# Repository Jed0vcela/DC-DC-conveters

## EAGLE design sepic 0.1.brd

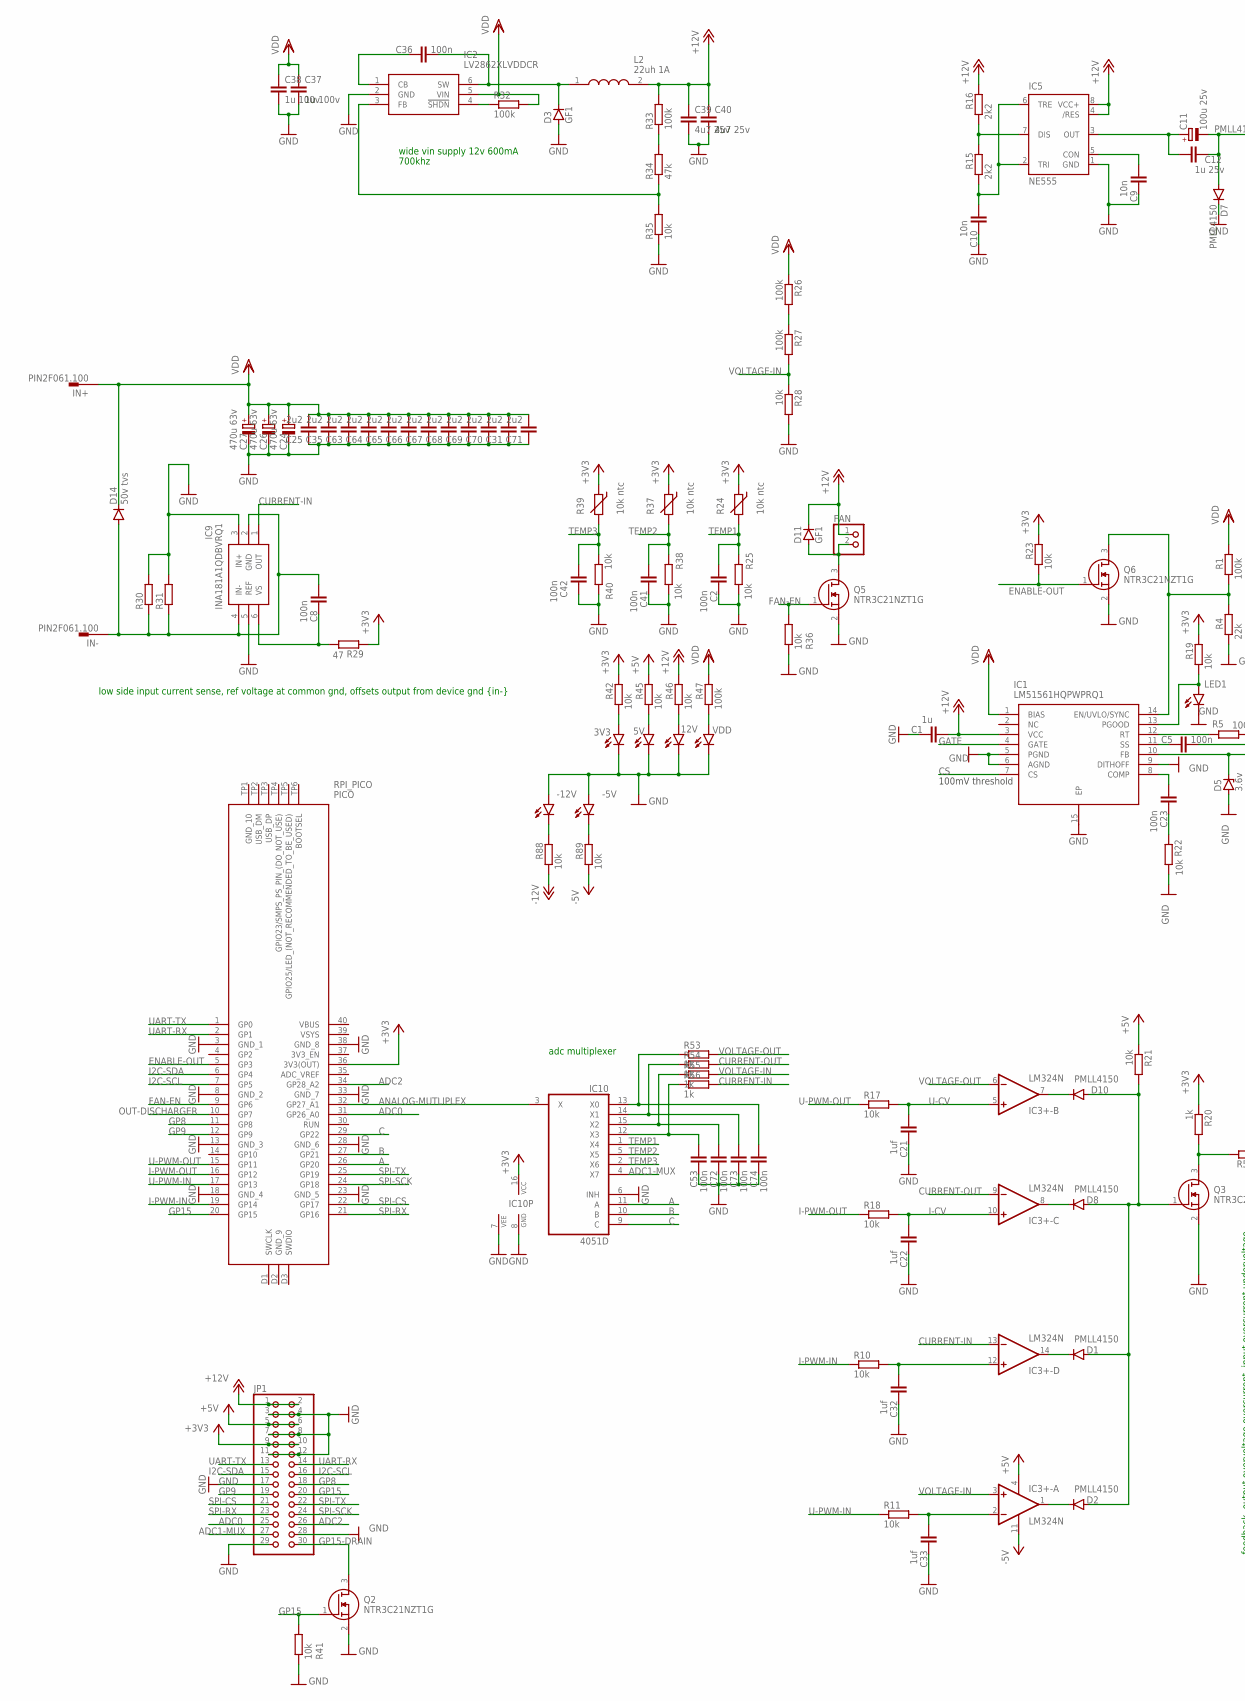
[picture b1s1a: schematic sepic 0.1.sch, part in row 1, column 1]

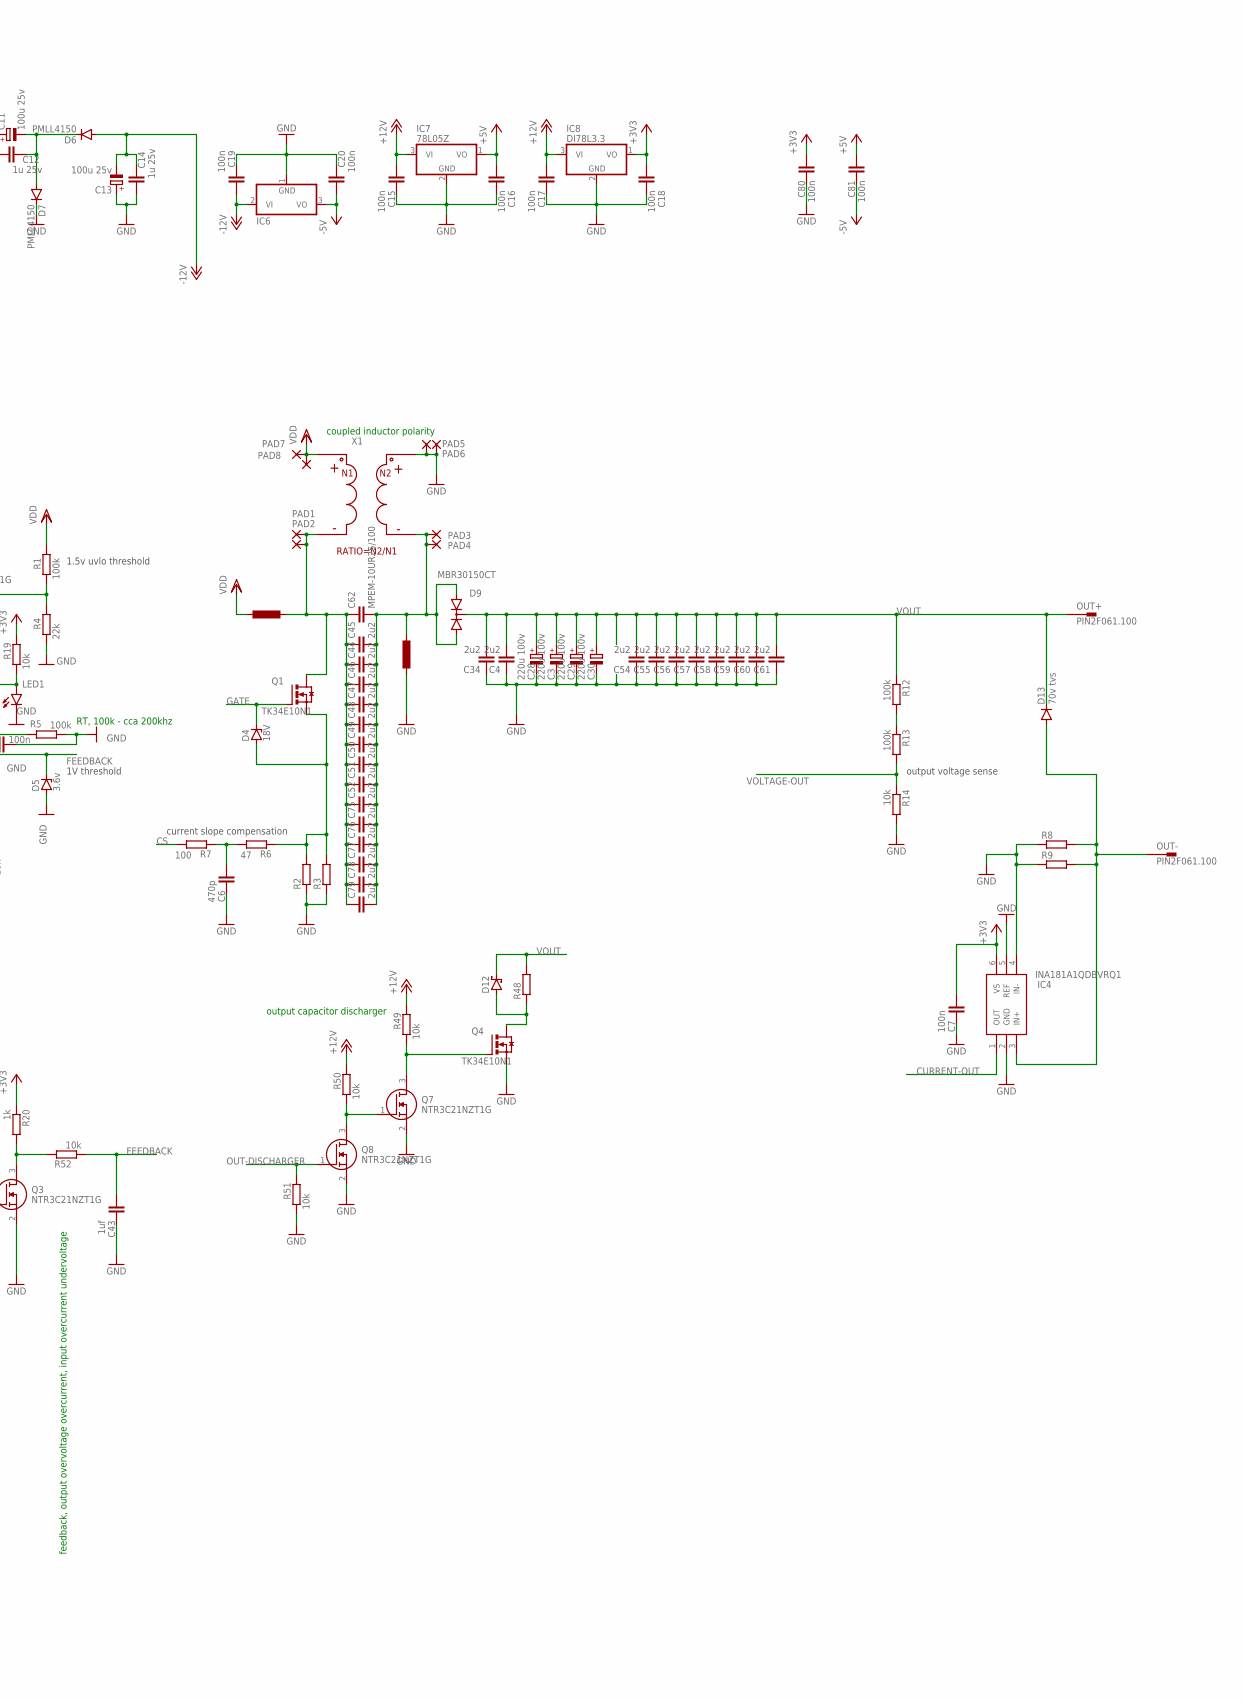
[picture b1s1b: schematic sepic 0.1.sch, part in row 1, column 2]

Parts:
3V3, 5V, 12V: LEDSML0805; SML0805
-5V, -12V: LEDSML0805; SML0805
C1: 1u; C0805
C2, C5, C7, C8, C15, C16, C17, C18, C19, C20, C23, C36, C41, C42, C53, C72, C73, C74, C80, C81: 100n; C0805
C3, C28, C29, C30: 220u 100v; E7,5-16
C4, C25, C31, C34, C35, C44, C45, C46, C47, C48, C49, C50, C51, C52, C54, C55, C56, C57, C58, C59, C60, C61, C63, C64, C65, C66, C67, C68, C69, C70, C71, C75, C76, C77, C78, C79: 2u2; C1210
C6: 470p; C0805
C9, C10: 10n; C0805
C11, C13: 100u 25v; E5-8,5
C12, C14: 1u 25v; C0805
C21, C22, C32, C33, C43: 1uf; C0805
C24, C26, C27: 470u 63v; E7,5-16
C37, C38: 1u 100v; C1206
C39, C40: 4u7 25v; C1206
C62: MPEM-10UR25/100; C225-108X268
D1, D2, D6, D7, D8, D10: PMLL4150; SOD80C
D3, D11: GF1; SMA-DO214AC
D4: 18V; SOD80C
D5: 3.6v; SOD80C
D9: MBR30150CT; IW220ABS
D12: SCHOTTKY-DIODESMD; SMB
D13: 70v tvs; DO15-12
D14: 50v tvs; DO15-12
FAN: PINHD-1X2; 1X02
IC1: LM51561HQPWPRQ1; SOP65P640X120-15N
IC2: LV2862XLVDDCR; SOT95P280X110-6N
IC3+-: LM324N; DIL14
IC4, IC9: INA181A1QDBVRQ1; SOT95P280X145-6N
IC5: NE555; DIL-08
IC6: 79L05Z; TO92
IC7: 78L05Z; TO92
IC8: DI78L3.3; TO92
IC10: 4051D; SO16
IN+: PIN2F061.100; F061.100
IN-: PIN2F061.100; F061.100
JP1: PINHD-2X15; 2X15
L2: 22uh 1A; DER070547
LED1: LEDSML0805; SML0805
OUT+: PIN2F061.100; F061.100
OUT-: PIN2F061.100; F061.100
PAD1, PAD2, PAD3, PAD4, PAD5, PAD6, PAD7, PAD8: 3,17/1,1
Q1, Q4: TK34E10N1; TO262-V
Q2, Q3, Q5, Q6, Q7, Q8: NTR3C21NZT1G; SOT96P237X111-3N
R1, R5, R12, R13, R26, R27, R32, R33, R47: 100k; R0805
R2, R3, R8, R9, R30, R31: R-EU_R2512; R2512
R4: 22k; R0805
R6, R29: 47; R0805
R7: 100; R0805
R10, R11, R14, R17, R18, R19, R21, R22, R23, R25, R28, R35, R36, R38, R40, R41, R42, R45, R46, R49, R50, R51, R52, R88, R89: 10k; R0805
R15, R16: 2k2; R0805
R20, R53, R54, R55, R56: 1k; R0805
R24, R37, R39: 10k ntc; RS-2,5
R34: 47k; R0805
R48: R-EU_0817/22; P0817/22
RPI_PICO: PICO
VDD: LEDSML0805; SML0805

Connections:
+3V3: C7.2, C18.2, C80.2, IC4.6 (VS), IC8.1 (VO), IC10.16 (VCC), JP1.9, JP1.10, R19.2, R20.1, R23.2, R24.1, R29.1, R37.1, R39.1, R42.2, RPI_PICO.36 (3V3(OUT))
+5V: C16.2, C81.2, IC3+-.4 (V+), IC7.1 (VO), JP1.5, JP1.6, R21.1, R45.2
+12V: C1.2, C15.2, C17.2, C39.1, C40.1, D11.K (C), FAN.1, IC1.3 (VCC), IC5.4 (/RES), IC5.8 (VCC+), IC7.3 (VI), IC8.3 (VI), JP1.1, JP1.2, L2.2, R16.2, R33.2, R46.2, R49.2, R50.2
-5V: C20.1, C81.1, IC3+-.11 (V-), IC6.3 (VO), R89.1
-12V: C13.-, C14.1, C19.1, D6.A, IC6.2 (VI), R88.1
A: IC10.11 (A), RPI_PICO.26 (GP20)
ADC0: JP1.25, RPI_PICO.31 (GP26_A0)
ADC1-MUX: IC10.4 (X7), JP1.27
ADC2: JP1.26, RPI_PICO.34 (GP28_A2)
ANALOG-MUTLIPLEX: IC10.3 (X), RPI_PICO.32 (GP27_A1)
B: IC10.10 (B), RPI_PICO.27 (GP21)
C: IC10.9 (C), RPI_PICO.29 (GP22)
CS: IC1.7 (CS), R7.2
CS1: D4.A, Q1.3 (S), R2.2, R3.2, R6.1
CURRENT-IN: IC3+-.13 (-IN), IC9.1 (OUT), R56.2
CURRENT-OUT: IC3+-.9 (-IN), IC4.1 (OUT), R54.2
ENABLE-OUT: Q6.1 (G), R23.1, RPI_PICO.5 (GP3)
FAN-EN: Q5.1 (G), R36.2, RPI_PICO.9 (GP6)
FEEDBACK: C43.2, D5.C, IC1.10 (FB), R52.1
GATE: D4.C, IC1.4 (GATE), Q1.1 (G)
GND: 3V3.C, 5V.C, 12V.C, -5V.A, -12V.A, C1.1, C2.1, C3.-, C4.1, C5.2, C6.1, C7.1, C9.1, C10.1, C13.+, C14.2, C15.1, C16.1, C17.1, C18.1, C19.2, C20.2, C21.1, C22.1, C24.-, C25.1, C26.-, C27.-, C28.-, C29.-, C30.-, C31.1, C32.1, C33.1, C34.1, C35.1, C37.2, C38.2, C39.2, C40.2, C41.1, C42.1, C43.1, C53.1, C54.1, C55.1, C56.1, C57.1, C58.1, C59.1, C60.1, C61.1, C63.1, C64.1, C65.1, C66.1, C67.1, C68.1, C69.1, C70.1, C71.1, C72.1, C73.1, C74.1, C80.1, D3.A, D5.A, D7.C, IC1.5 (PGND), IC1.6 (AGND), IC1.9 (DITHOFF), IC1.15 (EP), IC2.2 (GND), IC4.2 (GND), IC4.4 (IN-), IC4.5 (REF), IC5.1 (GND), IC6.1 (GND), IC7.2 (GND), IC8.2 (GND), IC9.3 (IN+), IC9.5 (REF), IC10.6 (INH), IC10.7 (VEE), IC10.8 (GND), JP1.3, JP1.4, JP1.7, JP1.8, JP1.11, JP1.12, JP1.17, JP1.28, JP1.29, LED1.C, PAD5.1, PAD6.1, Q2.2 (S), Q3.2 (S), Q4.3 (S), Q5.2 (S), Q6.2 (S), Q7.2 (S), Q8.2 (S), R2.1, R3.1, R4.1, R5.1, R8.1, R9.1, R14.2, R22.2, R25.1, R28.2, R30.2, R31.2, R35.1, R36.1, R38.1, R40.1, R41.1, R51.1, RPI_PICO.3 (GND_1), RPI_PICO.8 (GND_2), RPI_PICO.13 (GND_3), RPI_PICO.18 (GND_4), RPI_PICO.23 (GND_5), RPI_PICO.28 (GND_6), RPI_PICO.33 (GND_7), RPI_PICO.38 (GND_8), VDD.C
GP8: JP1.18, RPI_PICO.11 (GP8)
GP9: JP1.19, RPI_PICO.12 (GP9)
GP15: JP1.20, Q2.1 (G), R41.2, RPI_PICO.20 (GP15)
GP15-DRAIN: JP1.30, Q2.3 (D)
I2C-SCL: JP1.16, RPI_PICO.7 (GP5)
I2C-SDA: JP1.15, RPI_PICO.6 (GP4)
I-CV: C22.2, IC3+-.10 (+IN), R18.2
I-PWM-IN: R10.1, RPI_PICO.19 (GP14)
I-PWM-OUT: R18.1, RPI_PICO.16 (GP12)
IN_GND: C8.2, D14.A, IC9.2 (GND), IC9.4 (IN-), IN-.A1, IN-.A2, R30.1, R31.1
unnamed: IC1.14 (EN/UVLO/SYNC), Q6.3 (D), R1.1, R4.2
unnamed: C44.1, C45.1, C46.1, C47.1, C48.1, C49.1, C50.1, C51.1, C52.1, C62.1, C75.1, C76.1, C77.1, C78.1, C79.1, PAD1.1, PAD2.1, Q1.2 (D)
unnamed: C44.2, C45.2, C46.2, C47.2, C48.2, C49.2, C50.2, C51.2, C52.2, C62.2, C75.2, C76.2, C77.2, C78.2, C79.2, D9.A1, D9.A2, PAD3.1, PAD4.1
unnamed: C6.2, R6.2, R7.1
unnamed: IC1.12 (RT), R5.2
unnamed: C5.1, IC1.11 (SS)
unnamed: C53.2, IC10.12 (X3), R56.1
unnamed: D10.C, IC3+-.7 (OUT)
unnamed: D1.C, IC3+-.14 (OUT)
unnamed: R12.2, R13.1
unnamed: IC5.7 (DIS), R15.2, R16.1
unnamed: C10.2, IC5.2 (TRI), IC5.6 (TRE), R15.1
unnamed: C9.2, IC5.5 (CON)
unnamed: C11.+, C12.2, IC5.3 (OUT)
unnamed: C11.-, C12.1, D6.C, D7.A
unnamed: D8.C, IC3+-.8 (OUT)
unnamed: D1.A, D2.A, D8.A, D10.A, Q3.1 (G), R21.2
unnamed: IC1.13 (PGOOD), LED1.A, R19.1
unnamed: C23.2, IC1.8 (COMP)
unnamed: C23.1, R22.1
unnamed: C32.2, IC3+-.12 (+IN), R10.2
unnamed: IC2.4 (!SHDN), R32.1
unnamed: C36.2, D3.K (C), IC2.6 (SW), L2.1
unnamed: D11.A, FAN.2, Q5.3 (D)
unnamed: C36.1, IC2.1 (CB)
unnamed: R26.2, R27.1
unnamed: C72.2, IC10.15 (X2), R55.1
unnamed: D2.C, IC3+-.1 (OUT)
unnamed: C8.1, IC9.6 (VS), R29.2
unnamed: C33.2, IC3+-.2 (-IN), R11.2
unnamed: R33.1, R34.2
unnamed: IC2.3 (FB), R34.1, R35.2
unnamed: 3V3.A, R42.1
unnamed: 5V.A, R45.1
unnamed: 12V.A, R46.1
unnamed: R47.1, VDD.A
unnamed: -5V.C, R89.2
unnamed: -12V.C, R88.2
unnamed: D12.A, Q4.2 (D), R48.1
unnamed: Q4.1 (G), Q7.3 (D), R49.1
unnamed: Q7.1 (G), Q8.3 (D), R50.1
unnamed: Q3.3 (D), R20.2, R52.2
unnamed: C73.2, IC10.14 (X1), R54.1
unnamed: C74.2, IC10.13 (X0), R53.1
OUT-DISCHARGER: Q8.1 (G), R51.2, RPI_PICO.10 (GP7)
OUT_GND: D13.A, IC4.3 (IN+), OUT-.A1, OUT-.A2, R8.2, R9.2
SPI-CS: JP1.21, RPI_PICO.22 (GP17)
SPI-RX: JP1.23, RPI_PICO.21 (GP16)
SPI-SCK: JP1.24, RPI_PICO.24 (GP18)
SPI-TX: JP1.22, RPI_PICO.25 (GP19)
TEMP1: C2.2, IC10.1 (X4), R24.2, R25.2
TEMP2: C41.2, IC10.5 (X5), R37.2, R38.2
TEMP3: C42.2, IC10.2 (X6), R39.2, R40.2
U-CV: C21.2, IC3+-.5 (+IN), R17.2
U-PWM-IN: R11.1, RPI_PICO.17 (GP13)
U-PWM-OUT: R17.1, RPI_PICO.15 (GP11)
UART-RX: JP1.14, RPI_PICO.2 (GP1)
UART-TX: JP1.13, RPI_PICO.1 (GP0)
VDD: C24.+, C25.2, C26.+, C27.+, C31.2, C35.2, C37.1, C38.1, C63.2, C64.2, C65.2, C66.2, C67.2, C68.2, C69.2, C70.2, C71.2, D14.C, IC1.1 (BIAS), IC2.5 (VIN), IN+.A1, IN+.A2, PAD7.1, PAD8.1, R1.2, R26.1, R32.2, R47.2
VOLTAGE-IN: IC3+-.3 (+IN), R27.2, R28.1, R55.2
VOLTAGE-OUT: IC3+-.6 (-IN), R13.2, R14.1, R53.2
VOUT: C3.+, C4.2, C28.+, C29.+, C30.+, C34.2, C54.2, C55.2, C56.2, C57.2, C58.2, C59.2, C60.2, C61.2, D9.C, D12.C, D13.C, OUT+.A1, OUT+.A2, R12.1, R48.2

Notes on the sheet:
1.5v uvlo threshold
100mV threshold
current slope compensation
1V threshold
output voltage sense
RT, 100k - cca 200khz
coupled inductor polarity
low side input current sense, ref voltage at common gnd, offsets output from device gnd {in-}
adc multiplexer
feedback, output overvoltage overcurrent, input overcurrent undervoltage
wide vin supply 12v 600mA
700khz
output capacitor discharger

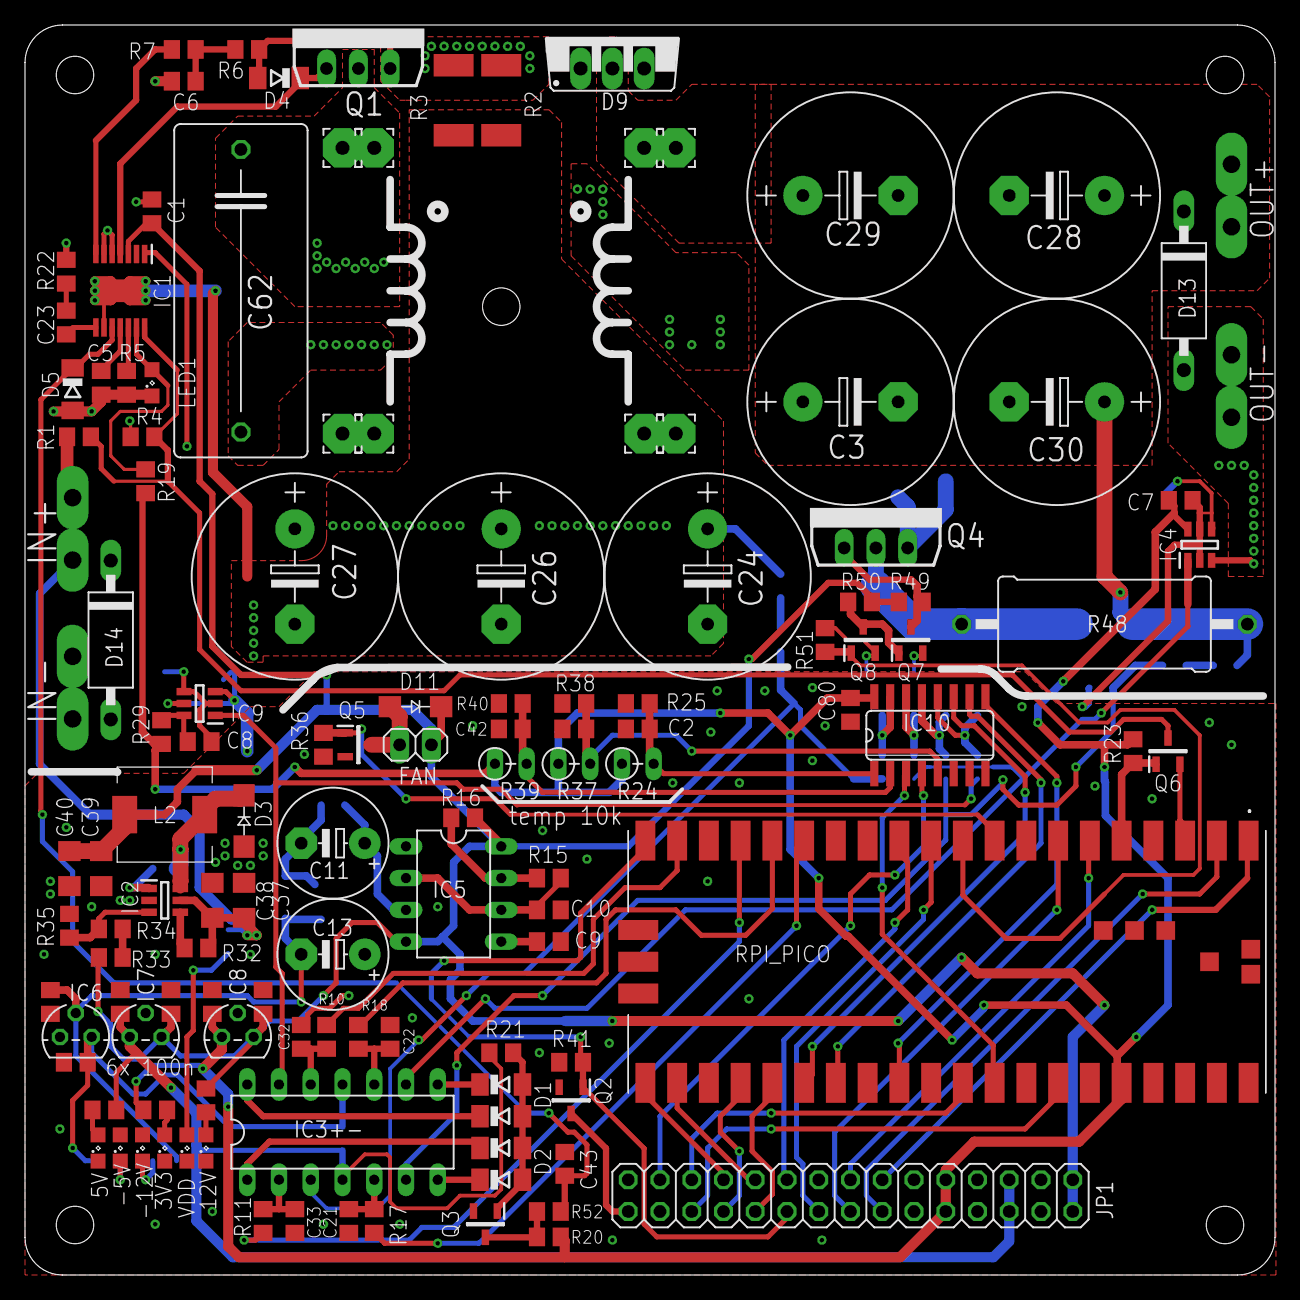
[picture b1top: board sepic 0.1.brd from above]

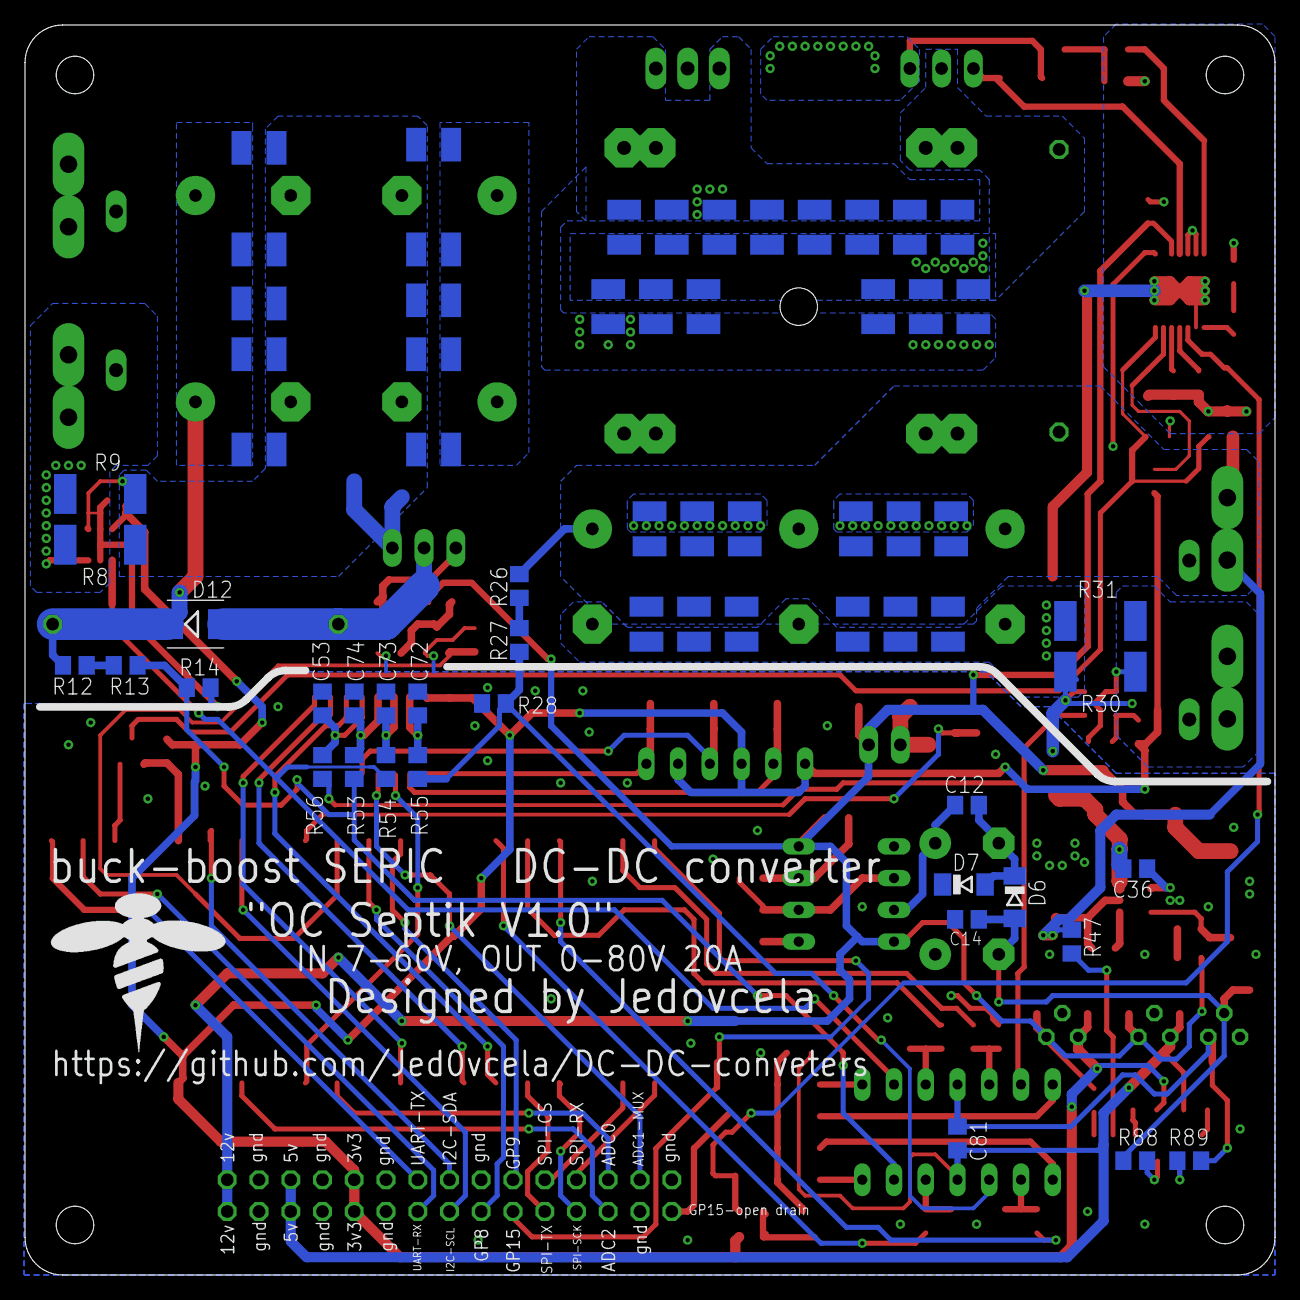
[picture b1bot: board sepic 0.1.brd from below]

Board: 2 copper layers, 100.0 x 100.0 mm, 192 parts (64 on the bottom side), 93 nets.
